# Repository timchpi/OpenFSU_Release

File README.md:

# OpenFSU_Release
 Release repo for OpenFSU
 Fire Sequencing Unit for Custom Electric-Blowback Replicas, as well as standard AEGs with more spacious battery compartments.

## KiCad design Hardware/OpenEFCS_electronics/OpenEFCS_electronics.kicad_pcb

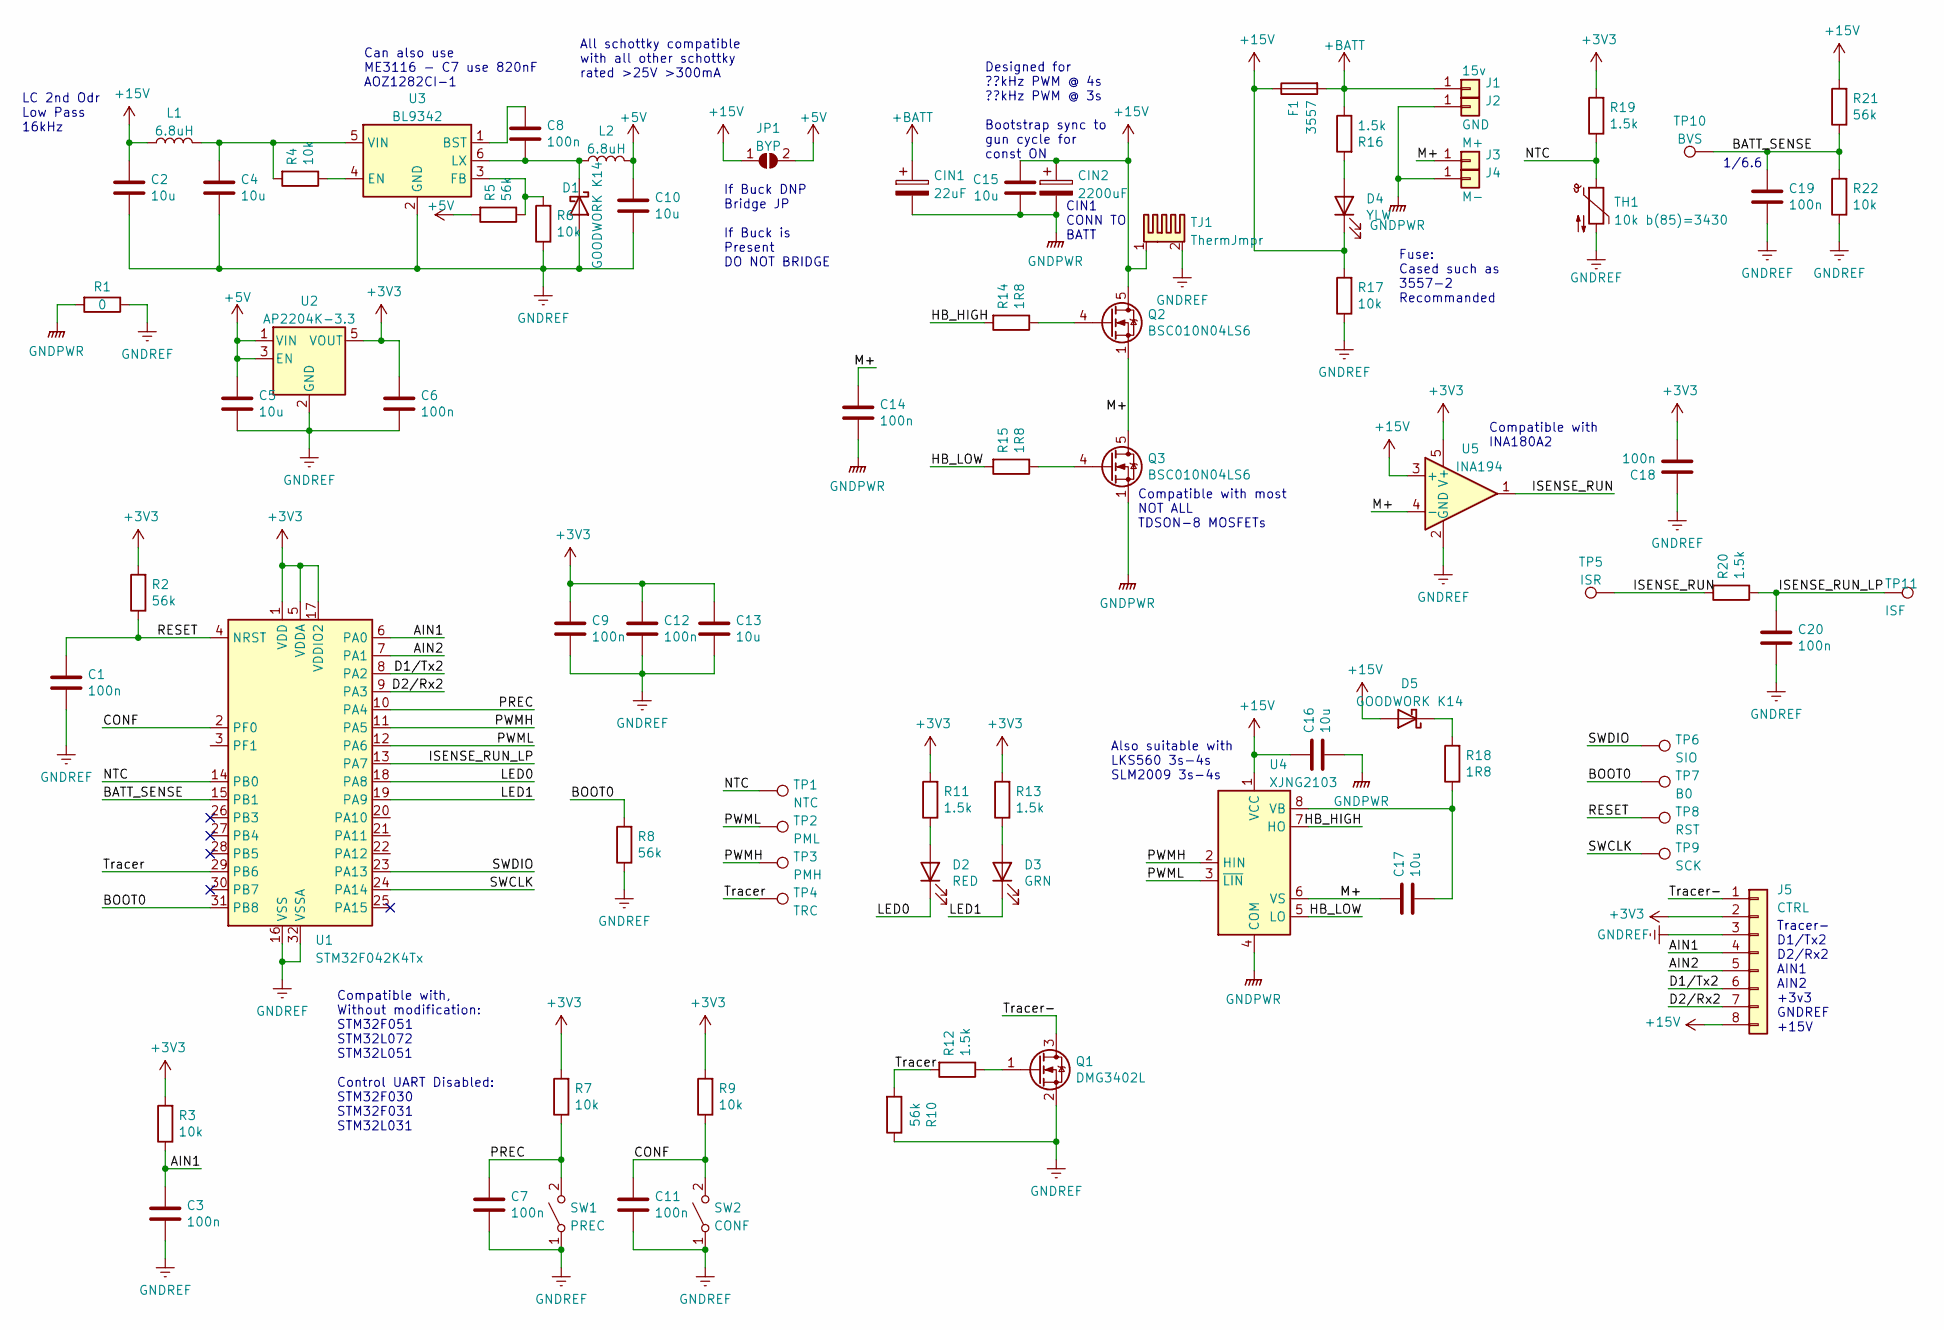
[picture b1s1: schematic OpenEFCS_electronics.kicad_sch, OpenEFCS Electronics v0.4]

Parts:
C1, C3, C6, C7, C8, C9, C11, C12, C14, C18, C19, C20: 100n; C_0603_1608Metric
C2, C4, C5, C10, C13, C15, C16, C17: 10u; C_0805_2012Metric
CIN1: 22uF; CP_EIA-3528-12_Kemet-T
CIN2: 2200uF
D1, D5: GOODWORK K14; D_SOD-123
D2: RED; LED_0603_1608Metric
D3: GRN; LED_0603_1608Metric
D4: YLW; LED_0603_1608Metric
F1: 3557; Keystone 3557
J1: 15v; SolderWirePad_1x01_SMD_1x2mm
J2: GND; SolderWirePad_1x01_SMD_1x2mm
J3: M+; SolderWirePad_1x01_SMD_1x2mm
J4: M-; SolderWirePad_1x01_SMD_1x2mm
J5: CTRL; JST_PH_B8B-PH-K_1x08_P2.00mm_Vertical
JP1: BYP; SolderJumper-2_P1.3mm_Open_TrianglePad1.0x1.5mm
L1, L2: 6.8uH; L_0805_2012Metric
Q1: DMG3402L; SOT-23
Q2, Q3: BSC010N04LS6; TDSON-8-1
R1: 0; R_0603_1608Metric
R2, R5, R8, R10, R21: 56k; R_0603_1608Metric
R3, R4, R6, R7, R9, R17, R22: 10k; R_0603_1608Metric
R11, R12, R13, R16, R19, R20: 1.5k; R_0603_1608Metric
R14, R15, R18: 1R8; R_0603_1608Metric
SW1: PREC; SW_SPST_B3U-1000P
SW2: CONF; SW_SPST_B3U-1000P
TH1: 10k b(85)=3430; R_0603_1608Metric
TJ1: ThermJmpr; R_1206_3216Metric
TP1: NTC; TestPoint_Pad_1.0x1.0mm
TP2: PML; TestPoint_Pad_1.0x1.0mm
TP3: PMH; TestPoint_Pad_1.0x1.0mm
TP4: TRC; TestPoint_Pad_1.0x1.0mm
TP5: ISR; TestPoint_Pad_1.0x1.0mm
TP6: SIO; TestPoint_Pad_1.0x1.0mm
TP7: B0; TestPoint_Pad_1.0x1.0mm
TP8: RST; TestPoint_Pad_1.0x1.0mm
TP9: SCK; TestPoint_Pad_1.0x1.0mm
TP10: BVS; TestPoint_Pad_1.0x1.0mm
TP11: ISF; TestPoint_Pad_1.0x1.0mm
U1: STM32F042K4Tx; LQFP-32_7x7mm_P0.8mm
U2: AP2204K-3.3; SOT-23-5
U3: BL9342; SOT-23-6
U4: XJNG2103; SOIC-8_3.9x4.9mm_P1.27mm
U5: INA194; SOT-23-5

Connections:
+3V3: C6.1, C9.1, C12.1, C13.1, C18.2, J5.2, R2.2, R3.2, R7.2, R9.2, R11.2, R13.2, R19.2, U1.1 (VDD), U1.5 (VDDA), U1.17 (VDDIO2), U2.5 (VOUT), U5.5 (V+)
+5V: C5.1, C10.1, JP1.2 (B), L2.2, R5.2, U2.1 (VIN), U2.3 (EN)
+15V: C2.1, C15.1, C16.1, CIN2.1, D4.1 (K), D5.2 (A), F1.1, J5.8, JP1.1 (A), L1.1, Q2.5 (D), R17.2, R21.2, TJ1.1, U4.1 (VCC), U5.3 (+)
+BATT: CIN1.1, F1.2, J1.1, R16.1
/AIN1: C3.1, J5.4, R3.1, U1.6 (PA0)
/AIN2: J5.5, U1.7 (PA1)
/BATT_SENSE: C19.1, R21.1, R22.2, TP10.1, U1.15 (PB1)
/BOOT0: R8.2, TP7.1, U1.31 (PB8)
/CONF: C11.1, R9.1, SW2.2 (B), U1.2 (PF0)
/D1/Tx2: J5.6, U1.8 (PA2)
/D2/Rx2: J5.7, U1.9 (PA3)
/HB_HIGH: R14.2, U4.7 (HO)
/HB_LOW: R15.2, U4.5 (LO)
/ISENSE_RUN: R20.2, TP5.1, U5.1
/ISENSE_RUN_LP: C20.1, R20.1, TP11.1, U1.13 (PA7)
/LED0: D2.1 (K), U1.18 (PA8)
/LED1: D3.1 (K), U1.19 (PA9)
/M+: C14.1, C17.1, J3.1, Q2.1 (S), Q2.2 (S), Q2.3 (S), Q3.5 (D), U4.6 (VS), U5.4 (-)
/NTC: R19.1, TH1.1, TP1.1, U1.14 (PB0)
/PREC: C7.1, R7.1, SW1.2 (B), U1.10 (PA4)
/PWMH: TP3.1, U1.11 (PA5), U4.2 (HIN)
/PWML: TP2.1, U1.12 (PA6), U4.3 (~LIN)
/RESET: C1.1, R2.1, TP8.1, U1.4 (NRST)
/SWCLK: TP9.1, U1.24 (PA14)
/SWDIO: TP6.1, U1.23 (PA13)
/Tracer: R10.2, R12.2, TP4.1, U1.29 (PB6)
/Tracer-: J5.1, Q1.3 (D)
GNDPWR: C14.2, C15.2, C16.2, CIN1.2, CIN2.2, J2.1, J4.1, Q3.1 (S), Q3.2 (S), Q3.3 (S), R1.2, U4.4 (COM)
GNDREF: C1.2, C2.2, C3.2, C4.2, C5.2, C6.2, C7.2, C9.2, C10.2, C11.2, C12.2, C13.2, C18.1, C19.2, C20.2, D1.2 (A), J5.3, Q1.2 (S), R1.1, R6.1, R8.1, R10.1, R17.1, R22.1, SW1.1 (A), SW2.1 (A), TH1.2, TJ1.2, U1.16 (VSS), U1.32 (VSSA), U2.2 (GND), U3.2 (GND), U5.2 (GND)
unnamed: C4.1, L1.2, R4.2, U3.5 (VIN)
unnamed: C8.1, U3.1 (BST)
unnamed: C8.2, D1.1 (K), L2.1, U3.6 (LX)
unnamed: C17.2, R18.1, U4.8 (VB)
unnamed: D2.2 (A), R11.1
unnamed: D3.2 (A), R13.1
unnamed: D4.2 (A), R16.2
unnamed: D5.1 (K), R18.2
unnamed: Q1.1 (G), R12.1
unnamed: Q2.4 (G), R14.1
unnamed: Q3.4 (G), R15.1
unnamed: R4.1, U3.4 (EN)
unnamed: R5.1, R6.2, U3.3 (FB)

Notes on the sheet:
Tracer- D1/Tx2 D2/Rx2 AIN1 AIN2 +3v3 GNDREF +15V
1/6.6
All schottky compatible with all other schottky rated >25V >300mA
If Buck DNP Bridge JP If Buck is Present DO NOT BRIDGE
Can also use ME3116 - C7 use 820nF AOZ1282CI-1
Fuse: Cased such as 3557-2 Recommanded
Designed for ??kHz PWM @ 4s ??kHz PWM @ 3s Bootstrap sync to gun cycle for const ON
Compatible with most NOT ALL TDSON-8 MOSFETs
Compatible with INA180A2
Also suitable with LKS560 3s-4s SLM2009 3s-4s
LC 2nd Odr Low Pass 16kHz
CIN1 CONN TO BATT
Compatible with, Without modification: STM32F051 STM32L072 STM32L051 Control UART Disabled: STM32F030 STM32F031 STM32L031

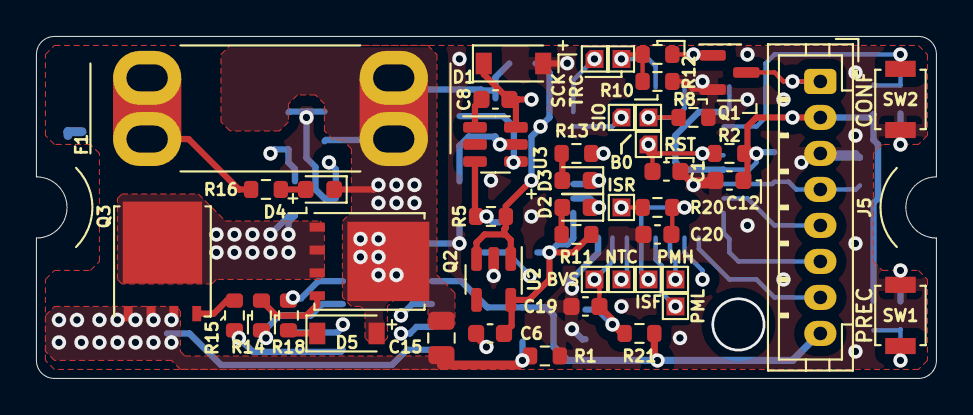
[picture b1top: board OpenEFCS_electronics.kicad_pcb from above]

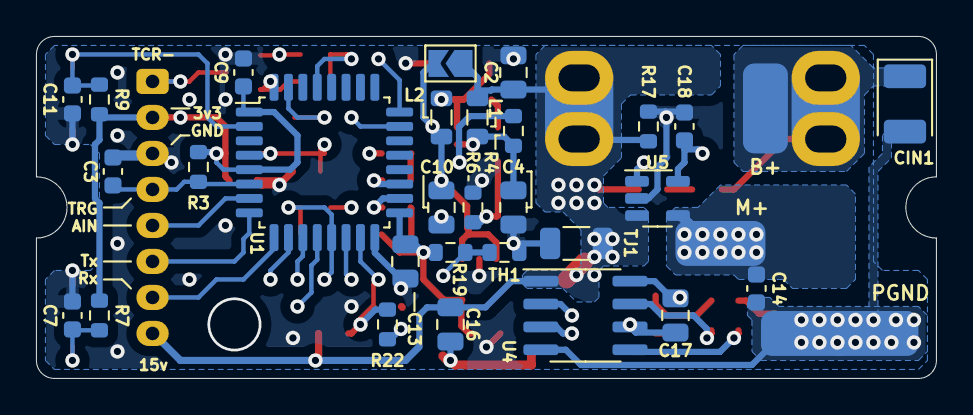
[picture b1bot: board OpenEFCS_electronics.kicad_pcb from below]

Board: 4 copper layers, 50.0 x 19.0 mm, 79 parts (33 on the bottom side), 42 nets.

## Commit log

2022-06-23 v0.3
2022-06-23 Updated minor BOM mistake
2022-06-29 Release v0.3.1
    Corrected footprint for INA2180
    Regenerated manufacturing files
2022-09-13 design complete for second prototype
2023-05-27 Removed current design
    Need ESD protection and transient spike protection.
    Will release updated design.
